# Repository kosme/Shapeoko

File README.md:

#Folder Structure#

##Upgrades##
Contains the folders of each of the upgrades

###xAxisPlate###
Upgrade for obtaining another 40mm of effective cutting length on the X axis by replacing the motor mount and the Z axis face plate.

##README.md##
This document in markdown format.

<br />This work is licensed under a <a rel="license" href="http://creativecommons.org/licenses/by-nc-sa/4.0/">Creative Commons Attribution-NonCommercial-ShareAlike 4.0 International License</a>.

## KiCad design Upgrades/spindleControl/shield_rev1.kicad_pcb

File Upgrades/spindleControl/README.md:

This shield implements several hacks for my Shapeoko CNC.

1. It disconnects the A-axis stepper motor signals. Now the source for that stepper are the Y-axis control signals. This enables to use a 2 motor Y-axis configuration.
2. It connects pin 11 of the Arduino to an optocoupler to control the spindle speed and activity.
3. It exposes pin 9, 10, and 12 so that they can be easily used to connect limit switches.
4. It exposes all the analog pins for custom implementations.
5. It provides a 5V and Gnd power rails to facilitate powering external accesories.

**Atention**

1. The pinout it uses is based on the original Arduino Stepper Shield. This pinout was later changed so this may not work with your shield.
2. It relies on a hack that connects the PWM signal for the spindle also to pin 12 on the Stepper Shield. This is not an elegant solution but does the trick since that pin is not connected to anything on the Stepper Shield.

All the files can be opened on Kicad 4+.

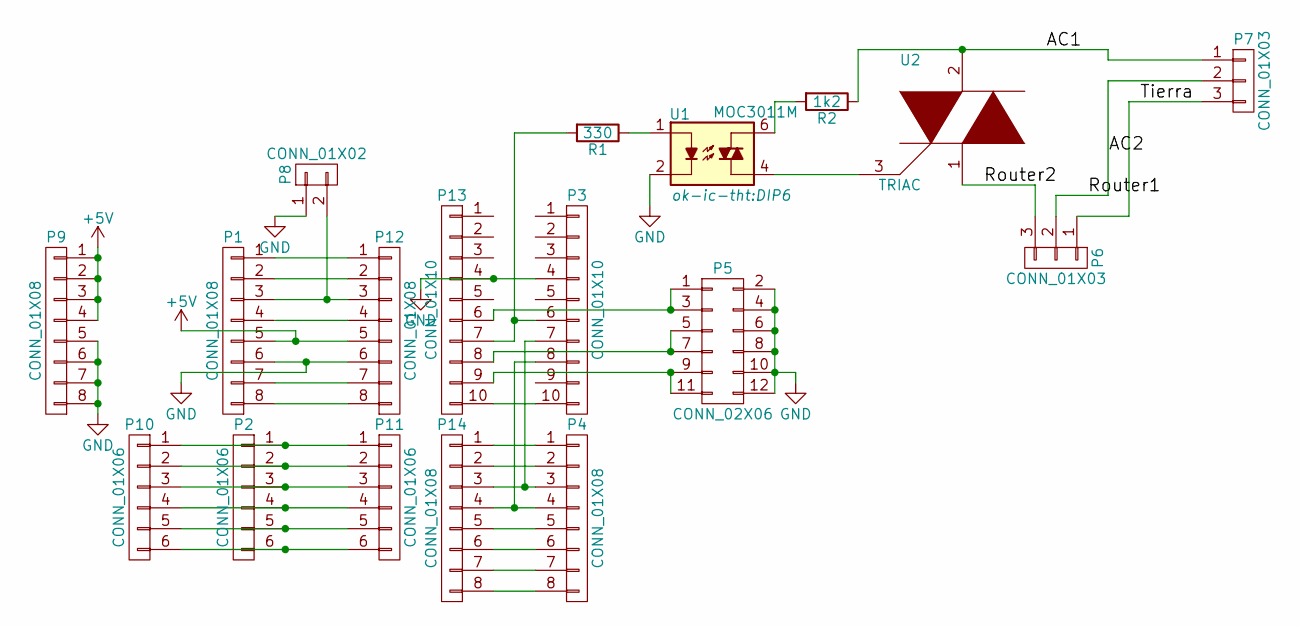
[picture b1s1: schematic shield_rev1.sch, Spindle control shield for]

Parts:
P1, P4, P9: CONN_01X08; Socket_Strip_Straight_1x08
P2, P10: CONN_01X06; Socket_Strip_Straight_1x06
P3: CONN_01X10; Socket_Strip_Straight_1x10
P5: CONN_02X06; Socket_Strip_Straight_2x06
P6, P7: CONN_01X03; AK300-3
P8: CONN_01X02; AK300-2
P11: CONN_01X06; Pin_Header_Straight_1x06
P12, P14: CONN_01X08; Pin_Header_Straight_1x08
P13: CONN_01X10; Pin_Header_Straight_1x10
R1: 330; Resistor_Horizontal_RM10mm
R2: 1k2; Resistor_Horizontal_RM10mm
U1: MOC3011M; DIP6
U2: TRIAC; TO-220_Neutral123_Horizontal_Reverse_LargePads

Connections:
+5V: P1.5, P9.1, P9.2, P9.3, P9.4, P12.5
/AC1: P7.1, R2.1, U2.2
/AC2: P6.2, P7.2
/Router2: P6.3, U2.1
/Tierra: P6.1, P7.3
GND: P1.6, P3.4, P5.2, P5.4, P5.6, P5.8, P5.10, P5.12, P8.1, P9.5, P9.6, P9.7, P9.8, P12.6, P13.4, U1.2
unnamed: P1.1, P12.1
unnamed: P1.2, P12.2
unnamed: P1.3, P8.2, P12.3
unnamed: P1.4, P12.4
unnamed: P1.7, P12.7
unnamed: P1.8, P12.8
unnamed: P2.1, P10.1, P11.1
unnamed: P2.2, P10.2, P11.2
unnamed: P2.3, P10.3, P11.3
unnamed: P2.4, P10.4, P11.4
unnamed: P2.5, P10.5, P11.5
unnamed: P2.6, P10.6, P11.6
unnamed: P5.1, P5.3, P13.6
unnamed: P3.6, P13.7, R1.2
unnamed: P5.5, P5.7, P13.8
unnamed: P5.9, P5.11, P13.9
unnamed: P3.10, P13.10
unnamed: P4.1, P14.1
unnamed: P4.2, P14.2
unnamed: P3.7, P4.3, P14.3
unnamed: P3.8, P4.4, P14.4
unnamed: P4.5, P14.5
unnamed: P4.6, P14.6
unnamed: P4.7, P14.7
unnamed: P4.8, P14.8
unnamed: R1.1, U1.1
unnamed: R2.2, U1.6
unnamed: U1.4, U2.3

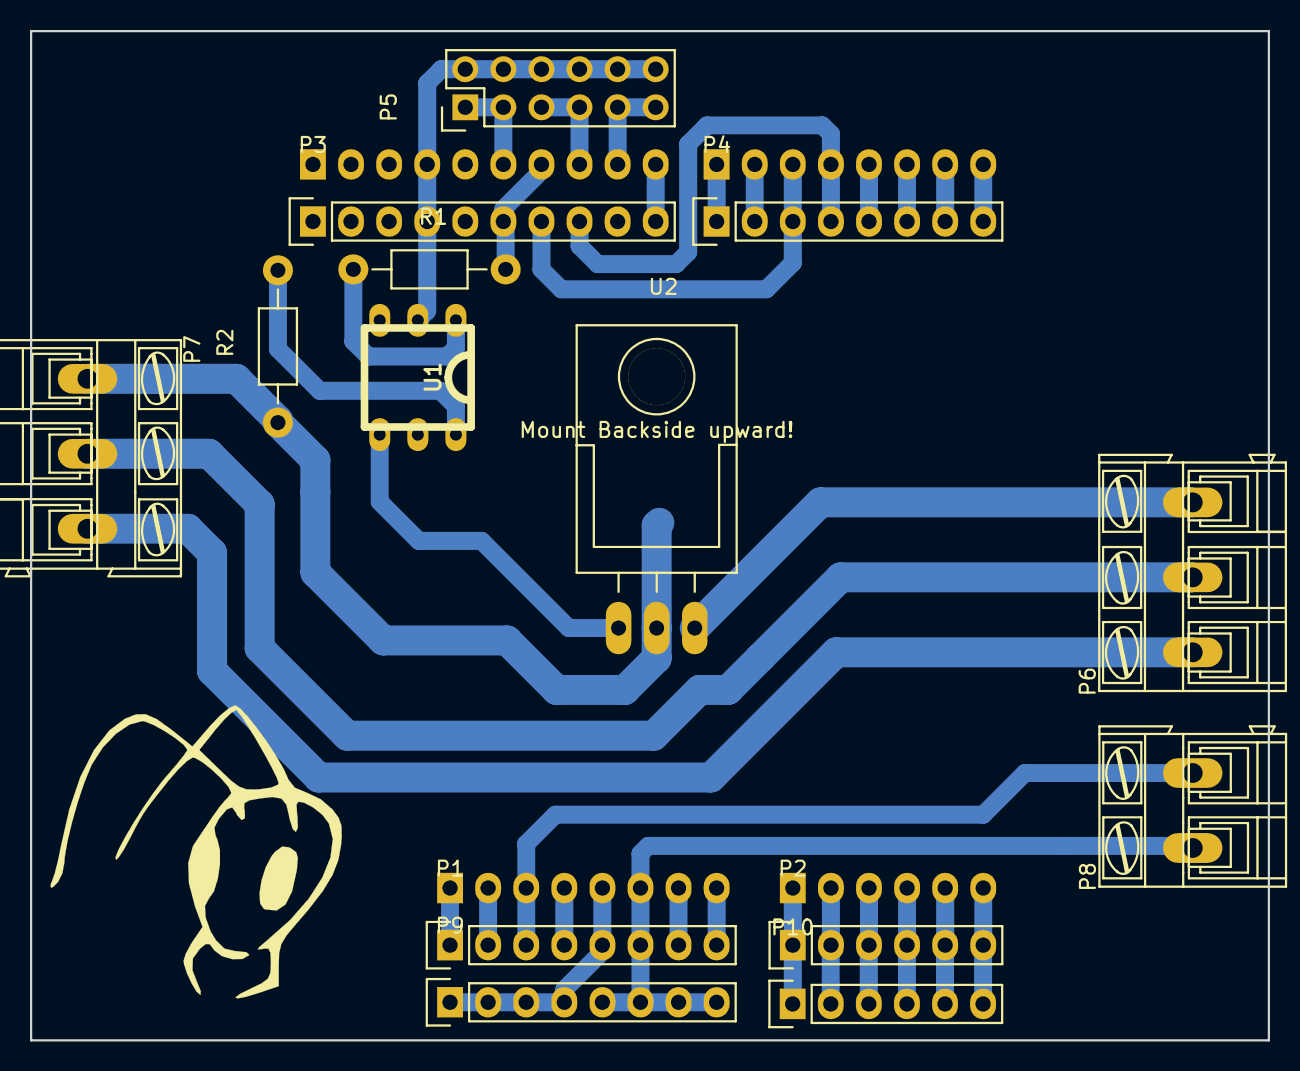
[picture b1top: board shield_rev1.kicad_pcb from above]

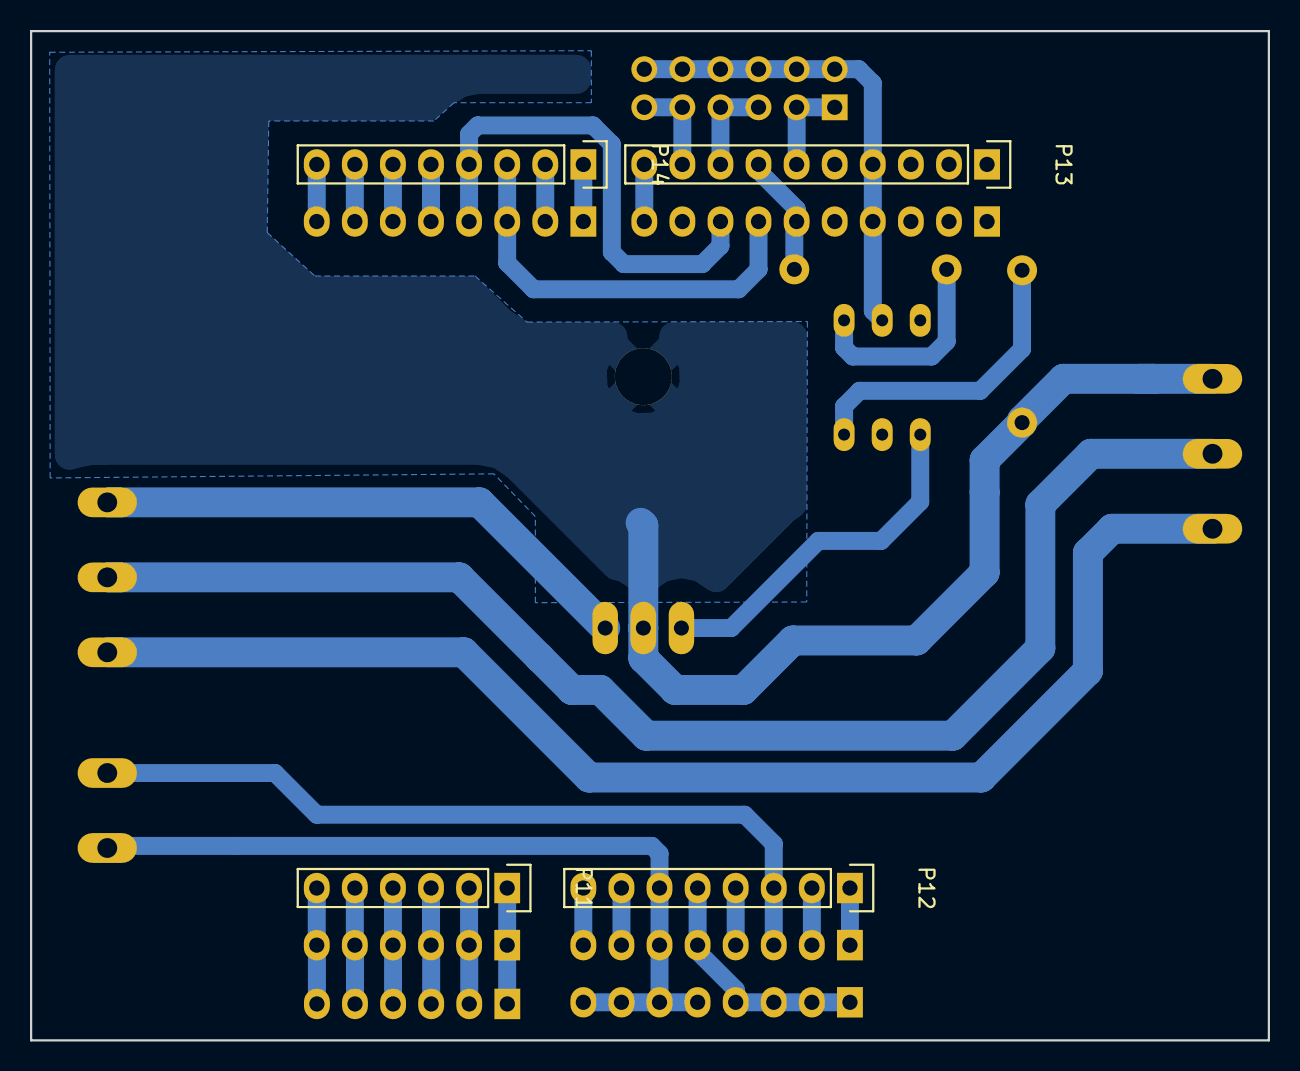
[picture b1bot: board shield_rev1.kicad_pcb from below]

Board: 2 copper layers, 82.5 x 67.3 mm, 18 parts (4 on the bottom side), 34 nets.

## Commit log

2014-10-09 - X-axis length upgrade.
2014-10-09 -ignore
2014-10-09 - License
2016-01-03 - Added aditional holes for pulley installation. - Changed motor mounting hole diameter to acomodate its protruding circle.
2016-03-12 Original plate and first revision
    Shorten the plate by 25 mm and remove one idler mounting hole
2016-03-12 Increase motor center hole diamater
2016-03-12 Reduce length and displace mouting holes
    - Reduce the plate length by 21 mm.
    - Move back the X axis mounting holes 35 mm to avoid the tool from
    hitting the front plate.
    - Move the X axis mounting holes 20 mm up to increase the movement range
    in Z
    - Increase the diameter of the central motor mounting hole so it can
2018-05-30 Development history
2018-05-30 Spindle control shield
2018-05-30 Fix offset layer and add holes for end stops
2018-05-31 Relocate shield files
2018-05-31 Comments on schematic
2018-07-18 Supports for endstops
